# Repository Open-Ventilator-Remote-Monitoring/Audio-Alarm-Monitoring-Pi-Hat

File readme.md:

## Audio Alarm Monitoring Raspberry Pi Hat
### Overview
This add-on circuit board (Pi Hat) provides a 2.5mm audio input jack to allow a Soundear audio monitoring device to interface with a raspberry pi configured to work with the [Open Ventilator Remote Monitoring Software](https://github.com/Open-Ventilator-Remote-Monitoring/remote-ventilator-monitor-pi). An indicator LED is illuminated when a 5V digital signal is received from the Soundear audio monitor. This PCB contains a voltage divider circuit which reduces the 5V digital output from the soundear monitor to 3.3v digital logic suitable for the raspberry pi.

### Inputs & Outputs
#### Inputs
* 2.5mm audio jack from cable connected to soundear (5V digital input)
* 5V power from raspberry pi
* Ground on raspberry pi

#### Outputs
* GPIO 4 pin on raspberry pi (3.3V digital output)

#### Bill Of Materials
The Bill of Materials is in the [Audio Alarm Monitoring Pi Hat.csv](https://github.com/Open-Ventilator-Remote-Monitoring/Audio-Alarm-Monitoring-Pi-Hat/blob/master/Audio%20Alarm%20Monitoring%20Pi%20Hat.csv) file

#### Manufacturing Notes
* This board has slotted holes for all the J1 pads. 
* Milling data is in Audio Alarm Monitoring Pi Hat.GML

#### Assembly Notes
* XA1 is an optional connector for an external LED. Do not populate D1 if you plan to use it.
* This hat connects to a Raspberry Pi using two 10mm tall standoffs. A third 10mm standoff can be connected to the hat and will sit ontop of the Raspberry Pi to add additional support.

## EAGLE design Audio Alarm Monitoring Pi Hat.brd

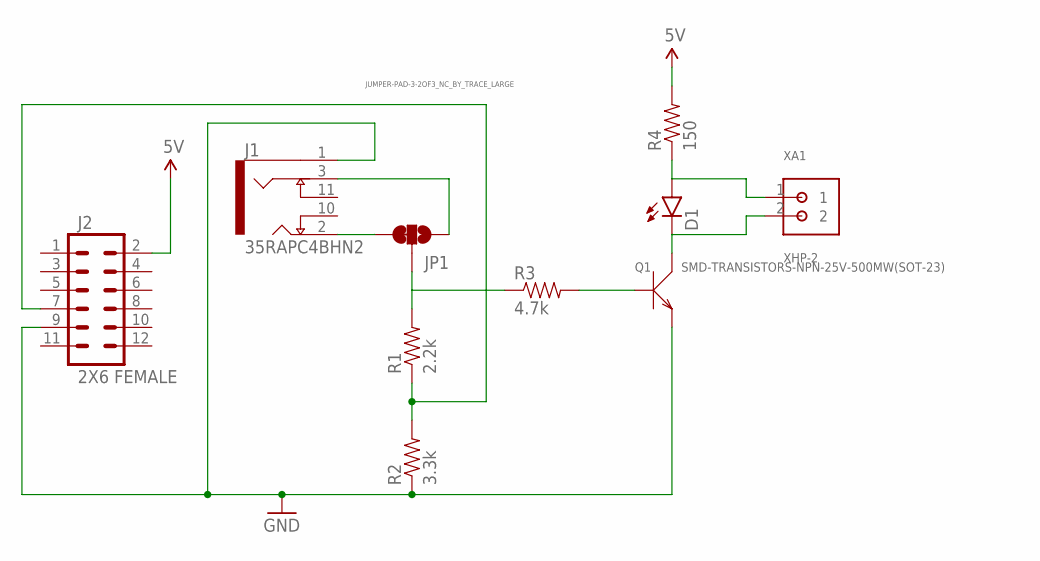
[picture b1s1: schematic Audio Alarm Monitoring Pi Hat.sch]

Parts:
D1: LED1206; LED-1206
J1: 35RAPC4BHN2; SWITCHCRAFT_35RAPC4BHN2
J2: 2X6 FEMALE; 2X6
JP1: JUMPER-PAD-3-2OF3_NC_BY_TRACE_LARGE; PAD-JUMPER-3-2OF3_NC_BY_TRACE_YES_SILK_LARGE
Q1: SMD-TRANSISTORS-NPN-25V-500MW(SOT-23); SOT-23
R1: 2.2k; 1206
R2: 3.3k; 1206
R3: 4.7k; 1206
R4: 150; 1206
XA1: XHP-2; JST_XHP-2

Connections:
5V: J2.2, R4.2
GND: J1.1, J2.9, Q1.2 (E), R2.1
unnamed: J2.7, R1.1, R2.2
unnamed: JP1.2, R1.2, R3.1
unnamed: J1.2, JP1.3
unnamed: D1.C, Q1.3 (C), XA1.2
unnamed: J1.3, JP1.1
unnamed: D1.A, R4.1, XA1.1
unnamed: Q1.1 (B), R3.2

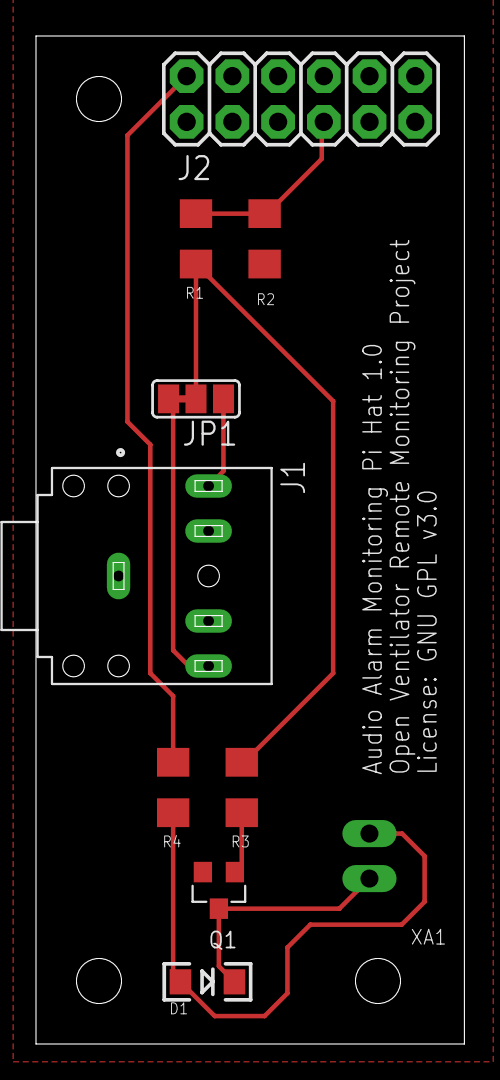
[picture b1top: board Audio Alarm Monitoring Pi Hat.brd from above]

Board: 2 copper layers, 23.8 x 56.0 mm, 10 parts (0 on the bottom side), 9 nets.

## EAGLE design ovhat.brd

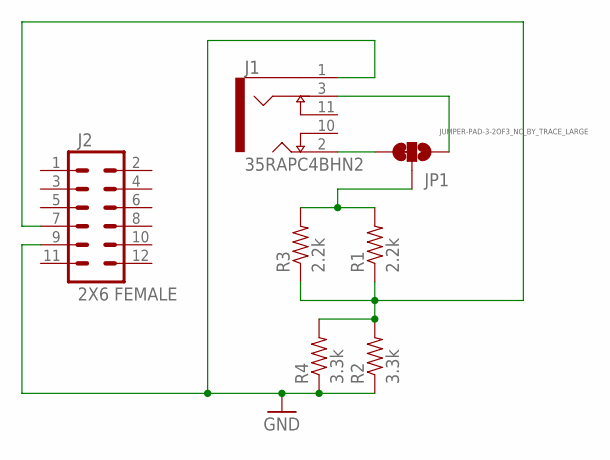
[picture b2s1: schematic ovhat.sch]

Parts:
J1: 35RAPC4BHN2; SWITCHCRAFT_35RAPC4BHN2
J2: 2X6 FEMALE; 2X6
JP1: JUMPER-PAD-3-2OF3_NC_BY_TRACE_LARGE; PAD-JUMPER-3-2OF3_NC_BY_TRACE_YES_SILK_LARGE
R1: 2.2k; AXIAL-0.4
R2: 3.3k; AXIAL-0.4
R3: 2.2k; 0805
R4: 3.3k; 0805

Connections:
GND: J1.1, J2.9, R2.P$1 (1), R4.1
unnamed: J2.7, R1.P$1 (1), R2.P$2 (2), R3.1, R4.2
unnamed: JP1.2, R1.P$2 (2), R3.2
unnamed: J1.2, JP1.3
unnamed: J1.3, JP1.1

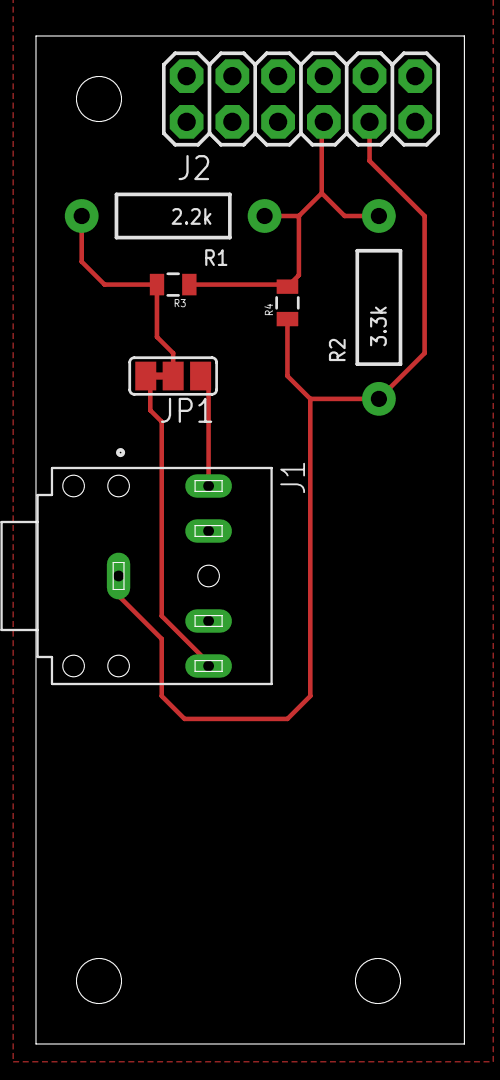
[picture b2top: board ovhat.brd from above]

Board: 2 copper layers, 23.8 x 56.0 mm, 7 parts (0 on the bottom side), 5 nets.

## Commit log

2020-04-22 Board with SMD and through hole parts
2020-04-22 Name Change
2020-04-22 Updating for LED + all surface mount resistors
2020-04-22 Added readme
2020-04-22 Removing .lck diles
2020-04-22 Added values layer to top sillscreen
2020-04-22 BOM + readme update
2020-04-22 Create LICENSE
2020-04-22 Update readme with board image

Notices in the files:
Audio Alarm Monitoring Pi Hat.brd:
License: GNU GPL v3.0
parts and their libraries:
SparkFun-Connectors: Licensing: Creative Commons ShareAlike 4.0 International - https://creativecommons.org/licenses/by-sa/4.0
